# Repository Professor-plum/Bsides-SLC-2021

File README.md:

# Bsides-SLC-2021
Bsides SLC 2021 Badge repository

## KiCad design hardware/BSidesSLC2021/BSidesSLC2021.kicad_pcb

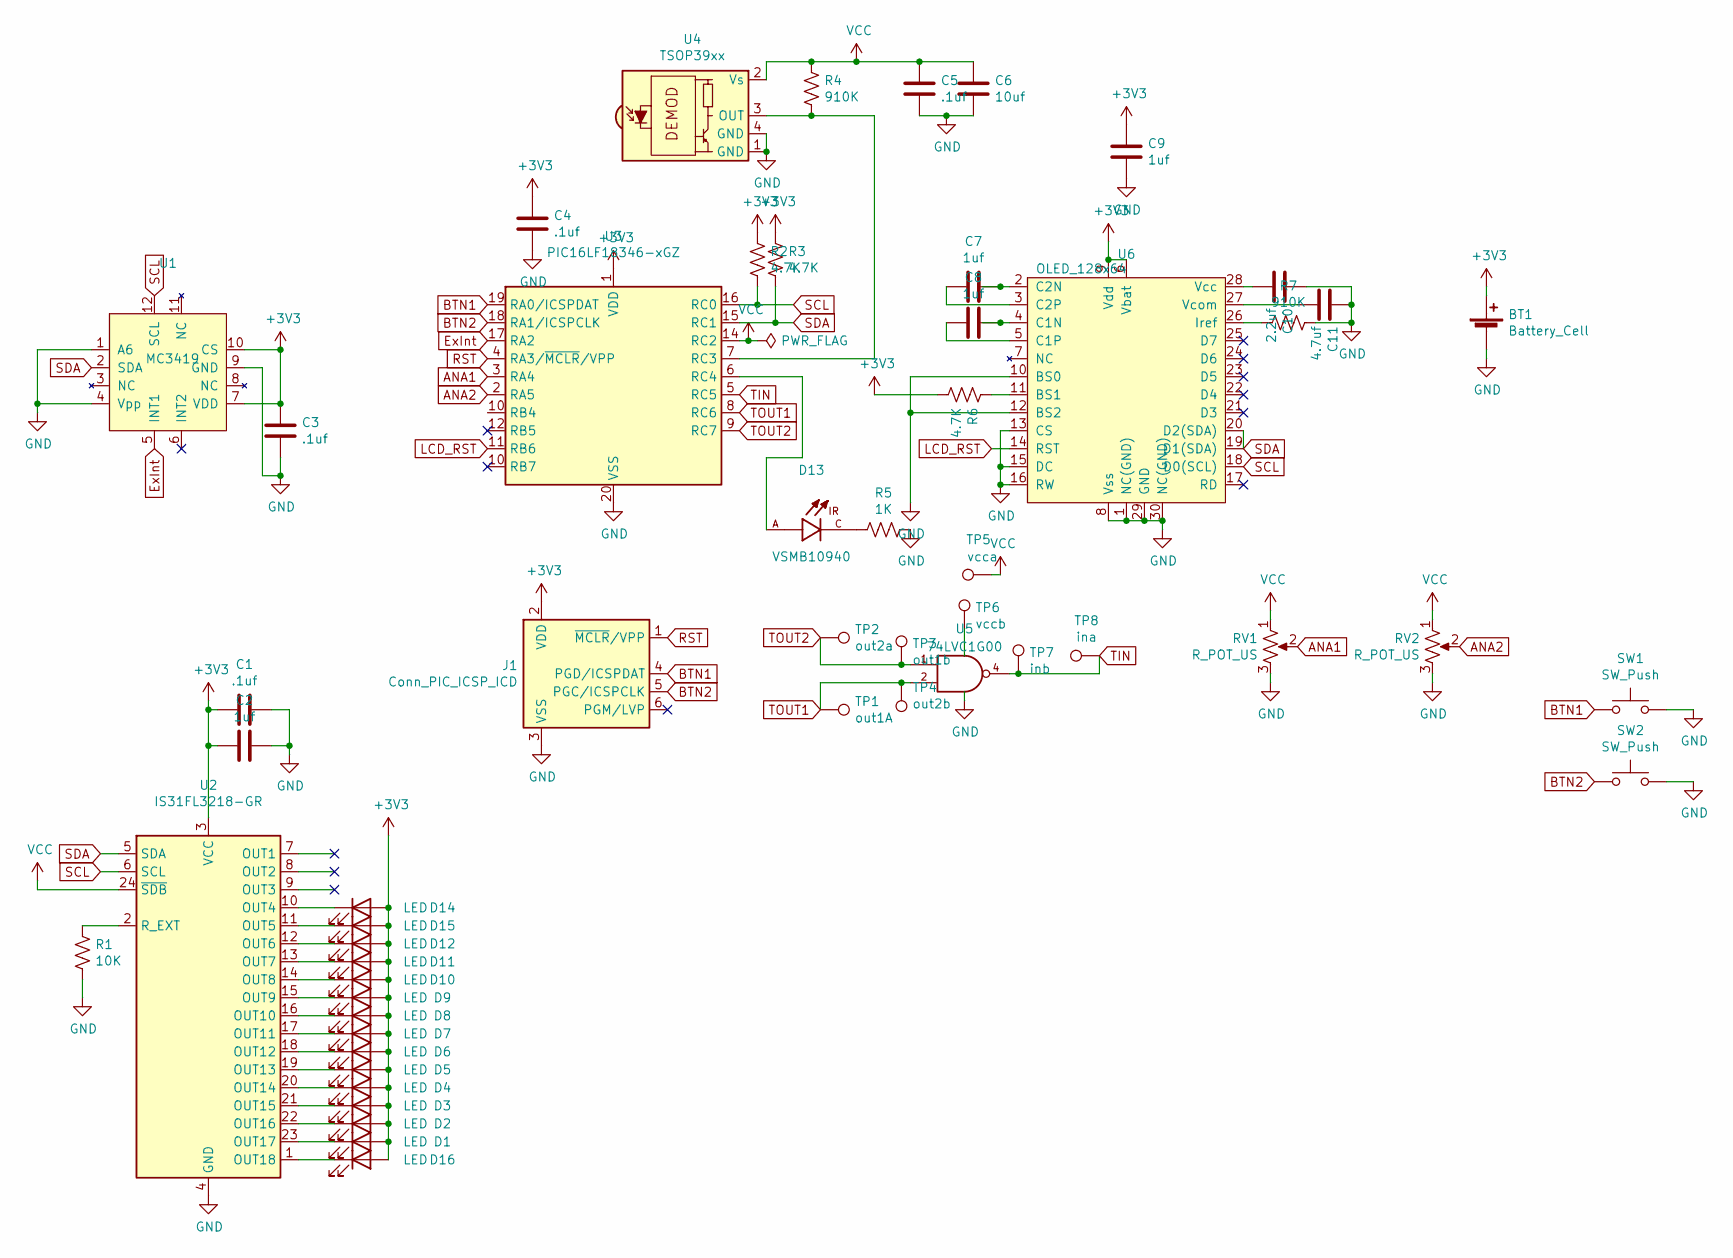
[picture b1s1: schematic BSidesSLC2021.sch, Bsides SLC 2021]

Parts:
BT1: Battery_Cell; BatteryHolder_Keystone_3034_1x20mm
C1, C3, C4, C5: .1uf; C_0603_1608Metric_Pad1.08x0.95mm_HandSolder
C2, C7, C8, C9: 1uf; C_0603_1608Metric_Pad1.08x0.95mm_HandSolder
C6: 10uf; C_0603_1608Metric_Pad1.08x0.95mm_HandSolder
C10: 2.2uf; C_0603_1608Metric_Pad1.08x0.95mm_HandSolder
C11: 4.7uf; C_0603_1608Metric_Pad1.08x0.95mm_HandSolder
D1, D2, D3, D4, D5, D6, D7, D8, D9, D10, D11, D12, D14, D15, D16: LED; LED_0603_1608Metric
D13: VSMB10940; DIO_VSMB10940; PARTREV 1.1
J1: Conn_PIC_ICSP_ICD; Batt_Conn5
R1: 10K; R_0603_1608Metric
R2, R3, R6: 4.7K; R_0603_1608Metric
R4, R7: 910K; R_0603_1608Metric
R5: 1K; R_0603_1608Metric
RV1, RV2: R_POT_US; Potentiometer_Bourns_PTV09A-1_Single_Vertical
SW1, SW2: SW_Push; SW_SPST_PTS645
TP1: out1A; TestPoint_Pad_D1.0mm
TP2: out2a; TestPoint_Pad_D1.0mm
TP3: out1b; TestPoint_Pad_D1.0mm
TP4: out2b; TestPoint_Pad_D1.0mm
TP5: vcca; TestPoint_Pad_D1.0mm
TP6: vccb; TestPoint_Pad_D1.0mm
TP7: inb; TestPoint_Pad_D1.0mm
TP8: ina; TestPoint_Pad_D1.0mm
U1: MC3419; LGA-12_2x2mm_P0.5mm
U2: IS31FL3218-GR; SOP-24_7.5x15.4mm_P1.27mm
U3: PIC16LF18346-xGZ; SSOP-20_5.3x7.2mm_P0.65mm
U4: TSOP39xx; TSOP392TR1
U5: 74LVC1G00; SOT-353_SC-70-5
U6: OLED_128x64; SSD1306_ribbon

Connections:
+3V3: BT1.1 (+), C1.1, C2.2, C3.2, C4.2, C9.2, D1.2 (A), D2.2 (A), D3.2 (A), D4.2 (A), D5.2 (A), D6.2 (A), D7.2 (A), D8.2 (A), D9.2 (A), D10.2 (A), D11.2 (A), D12.2 (A), D14.2 (A), D15.2 (A), D16.2 (A), J1.2 (VDD), R2.1, R3.1, R6.2, U1.7 (VDD), U1.10 (CS), U2.3 (VCC), U3.1 (VDD), U6.6 (Vbat), U6.9 (Vdd)
ANA1: RV1.2, U3.3 (RA4)
ANA2: RV2.2, U3.2 (RA5)
BTN1: J1.4 (PGD/ICSPDAT), SW1.1, U3.19 (RA0/ICSPDAT)
BTN2: J1.5 (PGC/ICSPCLK), SW2.1, U3.18 (RA1/ICSPCLK)
ExInt: U1.5 (INT1), U3.17 (RA2)
GND: BT1.2 (-), C1.2, C2.1, C3.1, C4.1, C5.1, C6.1, C9.1, C10.2, C11.2, J1.3 (VSS), R1.1, R5.1, R7.1, RV1.3, RV2.3, SW1.2, SW2.2, U1.1 (A6), U1.4 (Vpp), U1.9 (GND), U2.4 (GND), U3.20 (VSS), U4.1 (GND), U4.4 (GND), U5.3 (GND), U6.1 (NC(GND)), U6.8 (Vss), U6.10 (BS0), U6.12 (BS2), U6.13 (CS), U6.15 (DC), U6.16 (RW), U6.29 (GND), U6.30 (NC(GND))
LCD_RST: U3.11 (RB6), U6.14 (RST)
unnamed: C7.1, U6.2 (C2N)
unnamed: C7.2, U6.3 (C2P)
unnamed: C8.1, U6.4 (C1N)
unnamed: C8.2, U6.5 (C1P)
unnamed: C10.1, U6.28 (Vcc)
unnamed: C11.1, U6.27 (Vcom)
unnamed: D1.1 (K), U2.23 (OUT17)
unnamed: D2.1 (K), U2.22 (OUT16)
unnamed: D3.1 (K), U2.21 (OUT15)
unnamed: D4.1 (K), U2.20 (OUT14)
unnamed: D5.1 (K), U2.19 (OUT13)
unnamed: D6.1 (K), U2.18 (OUT12)
unnamed: D7.1 (K), U2.17 (OUT11)
unnamed: D8.1 (K), U2.16 (OUT10)
unnamed: D9.1 (K), U2.15 (OUT9)
unnamed: D10.1 (K), U2.14 (OUT8)
unnamed: D11.1 (K), U2.13 (OUT7)
unnamed: D12.1 (K), U2.12 (OUT6)
unnamed: D13.A, U3.6 (RC4)
unnamed: D13.C, R5.2
unnamed: D14.1 (K), U2.10 (OUT4)
unnamed: D15.1 (K), U2.11 (OUT5)
unnamed: D16.1 (K), U2.1 (OUT18)
unnamed: R1.2, U2.2 (R_EXT)
unnamed: R4.2, U3.7 (RC3), U4.3 (OUT)
unnamed: R6.1, U6.11 (BS1)
unnamed: R7.2, U6.26 (Iref)
RST: J1.1 (~MCLR~/VPP), U3.4 (RA3/~MCLR~/VPP)
SCL: R2.2, U1.12 (SCL), U2.6 (SCL), U3.16 (RC0), U6.18 (D0(SCL))
SDA: R3.2, U1.2 (SDA), U2.5 (SDA), U3.15 (RC1), U6.19 (D1(SDA)), U6.20 (D2(SDA))
TIN: TP7.1, TP8.1, U3.5 (RC5), U5.4
TOUT1: TP1.1, TP4.1, U3.8 (RC6), U5.2
TOUT2: TP2.1, TP3.1, U3.9 (RC7), U5.1

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
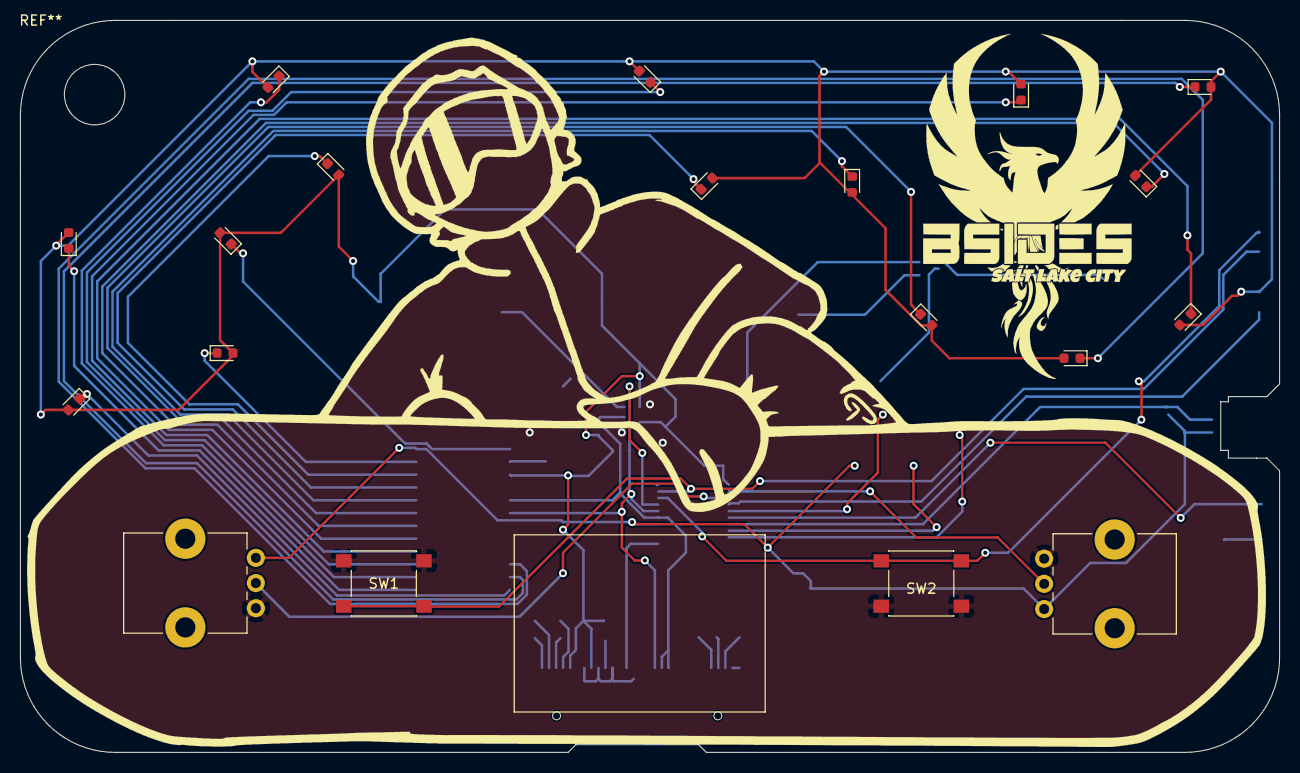
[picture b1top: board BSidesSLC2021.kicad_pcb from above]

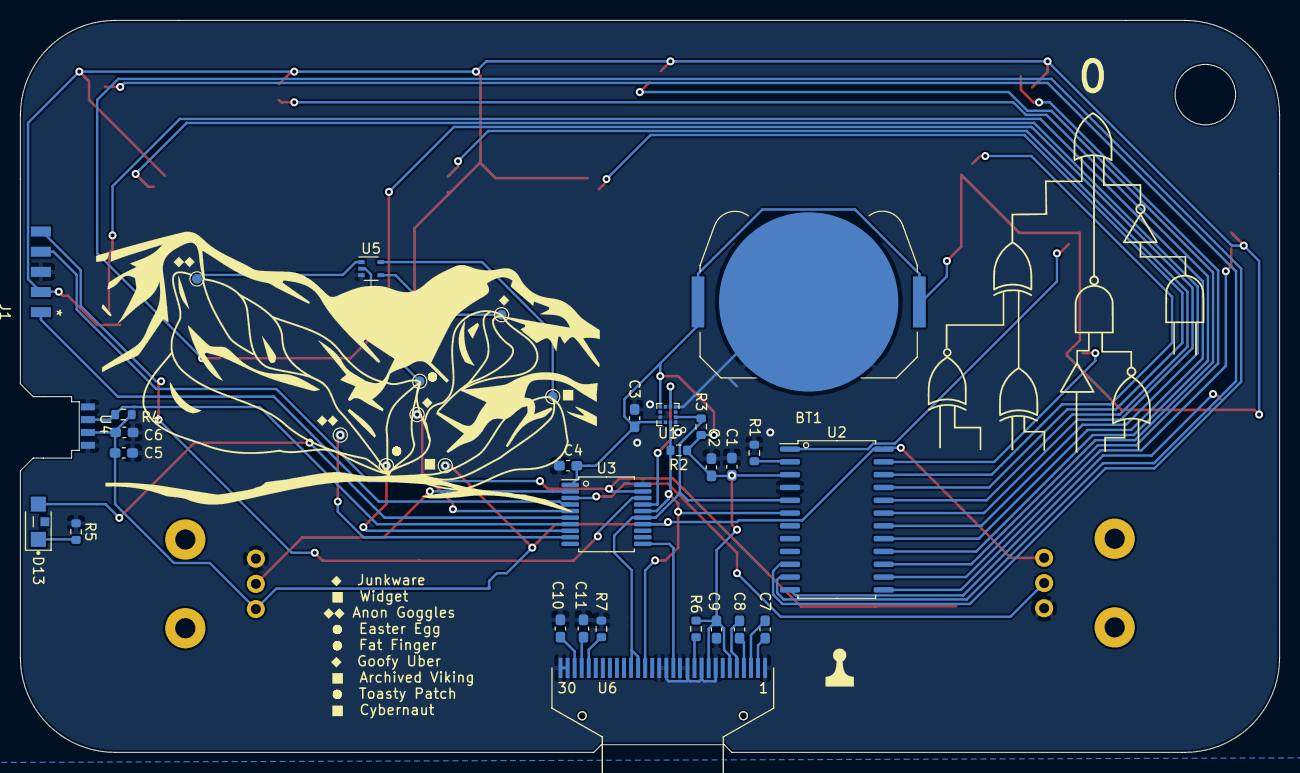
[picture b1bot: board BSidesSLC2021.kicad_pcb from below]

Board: 2 copper layers, 125.0 x 72.6 mm, 59 parts (38 on the bottom side), 42 nets.

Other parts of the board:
Ref**: Val**; logo_pheonix
Ref**#2: Val**; tree
Ref**#3: Val**; mtn2
Ref**#4: Val**; boarder
Ref**#5: Val**; plum

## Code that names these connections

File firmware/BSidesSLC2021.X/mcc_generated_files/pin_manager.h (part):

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// get/set IO_RA0 aliases
#define IO_RA0_TRIS                 TRISAbits.TRISA0
#define IO_RA0_LAT                  LATAbits.LATA0
#define IO_RA0_PORT                 PORTAbits.RA0
#define IO_RA0_WPU                  WPUAbits.WPUA0
#define IO_RA0_OD                   ODCONAbits.ODCA0
#define IO_RA0_ANS                  ANSELAbits.ANSA0
#define IO_RA0_SetHigh()            do { LATAbits.LATA0 = 1; } while(0)
#define IO_RA0_SetLow()             do { LATAbits.LATA0 = 0; } while(0)
#define IO_RA0_Toggle()             do { LATAbits.LATA0 = ~LATAbits.LATA0; } while(0)
#define IO_RA0_GetValue()           PORTAbits.RA0
#define IO_RA0_SetDigitalInput()    do { TRISAbits.TRISA0 = 1; } while(0)
#define IO_RA0_SetDigitalOutput()   do { TRISAbits.TRISA0 = 0; } while(0)
#define IO_RA0_SetPullup()          do { WPUAbits.WPUA0 = 1; } while(0)
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// get/set IO_RA1 aliases
#define IO_RA1_TRIS                 TRISAbits.TRISA1
#define IO_RA1_LAT                  LATAbits.LATA1
#define IO_RA1_PORT                 PORTAbits.RA1
#define IO_RA1_WPU                  WPUAbits.WPUA1
#define IO_RA1_OD                   ODCONAbits.ODCA1
#define IO_RA1_ANS                  ANSELAbits.ANSA1
#define IO_RA1_SetHigh()            do { LATAbits.LATA1 = 1; } while(0)
#define IO_RA1_SetLow()             do { LATAbits.LATA1 = 0; } while(0)
#define IO_RA1_Toggle()             do { LATAbits.LATA1 = ~LATAbits.LATA1; } while(0)
#define IO_RA1_GetValue()           PORTAbits.RA1
#define IO_RA1_SetDigitalInput()    do { TRISAbits.TRISA1 = 1; } while(0)
#define IO_RA1_SetDigitalOutput()   do { TRISAbits.TRISA1 = 0; } while(0)
#define IO_RA1_SetPullup()          do { WPUAbits.WPUA1 = 1; } while(0)
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#define RA2_SetHigh()            do { LATAbits.LATA2 = 1; } while(0)
#define RA2_SetLow()             do { LATAbits.LATA2 = 0; } while(0)
#define RA2_Toggle()             do { LATAbits.LATA2 = ~LATAbits.LATA2; } while(0)
#define RA2_GetValue()              PORTAbits.RA2
#define RA2_SetDigitalInput()    do { TRISAbits.TRISA2 = 1; } while(0)
#define RA2_SetDigitalOutput()   do { TRISAbits.TRISA2 = 0; } while(0)
#define RA2_SetPullup()             do { WPUAbits.WPUA2 = 1; } while(0)
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// get/set channel_ANA4 aliases
#define channel_ANA4_TRIS                 TRISAbits.TRISA4
#define channel_ANA4_LAT                  LATAbits.LATA4
#define channel_ANA4_PORT                 PORTAbits.RA4
#define channel_ANA4_WPU                  WPUAbits.WPUA4
#define channel_ANA4_OD                   ODCONAbits.ODCA4
#define channel_ANA4_ANS                  ANSELAbits.ANSA4
#define channel_ANA4_SetHigh()            do { LATAbits.LATA4 = 1; } while(0)
#define channel_ANA4_SetLow()             do { LATAbits.LATA4 = 0; } while(0)
#define channel_ANA4_Toggle()             do { LATAbits.LATA4 = ~LATAbits.LATA4; } while(0)
#define channel_ANA4_GetValue()           PORTAbits.RA4
#define channel_ANA4_SetDigitalInput()    do { TRISAbits.TRISA4 = 1; } while(0)
#define channel_ANA4_SetDigitalOutput()   do { TRISAbits.TRISA4 = 0; } while(0)
#define channel_ANA4_SetPullup()          do { WPUAbits.WPUA4 = 1; } while(0)
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// get/set channel_ANA5 aliases
#define channel_ANA5_TRIS                 TRISAbits.TRISA5
#define channel_ANA5_LAT                  LATAbits.LATA5
#define channel_ANA5_PORT                 PORTAbits.RA5
#define channel_ANA5_WPU                  WPUAbits.WPUA5
#define channel_ANA5_OD                   ODCONAbits.ODCA5
#define channel_ANA5_ANS                  ANSELAbits.ANSA5
#define channel_ANA5_SetHigh()            do { LATAbits.LATA5 = 1; } while(0)
#define channel_ANA5_SetLow()             do { LATAbits.LATA5 = 0; } while(0)
#define channel_ANA5_Toggle()             do { LATAbits.LATA5 = ~LATAbits.LATA5; } while(0)
#define channel_ANA5_GetValue()           PORTAbits.RA5
#define channel_ANA5_SetDigitalInput()    do { TRISAbits.TRISA5 = 1; } while(0)
#define channel_ANA5_SetDigitalOutput()   do { TRISAbits.TRISA5 = 0; } while(0)
#define channel_ANA5_SetPullup()          do { WPUAbits.WPUA5 = 1; } while(0)
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// get/set IO_RB6 aliases
#define IO_RB6_TRIS                 TRISBbits.TRISB6
#define IO_RB6_LAT                  LATBbits.LATB6
#define IO_RB6_PORT                 PORTBbits.RB6
#define IO_RB6_WPU                  WPUBbits.WPUB6
#define IO_RB6_OD                   ODCONBbits.ODCB6
#define IO_RB6_ANS                  ANSELBbits.ANSB6
#define IO_RB6_SetHigh()            do { LATBbits.LATB6 = 1; } while(0)
#define IO_RB6_SetLow()             do { LATBbits.LATB6 = 0; } while(0)
#define IO_RB6_Toggle()             do { LATBbits.LATB6 = ~LATBbits.LATB6; } while(0)
#define IO_RB6_GetValue()           PORTBbits.RB6
#define IO_RB6_SetDigitalInput()    do { TRISBbits.TRISB6 = 1; } while(0)
#define IO_RB6_SetDigitalOutput()   do { TRISBbits.TRISB6 = 0; } while(0)
#define IO_RB6_SetPullup()          do { WPUBbits.WPUB6 = 1; } while(0)
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#define RC0_SetHigh()            do { LATCbits.LATC0 = 1; } while(0)
#define RC0_SetLow()             do { LATCbits.LATC0 = 0; } while(0)
#define RC0_Toggle()             do { LATCbits.LATC0 = ~LATCbits.LATC0; } while(0)
#define RC0_GetValue()              PORTCbits.RC0
#define RC0_SetDigitalInput()    do { TRISCbits.TRISC0 = 1; } while(0)
#define RC0_SetDigitalOutput()   do { TRISCbits.TRISC0 = 0; } while(0)
#define RC0_SetPullup()             do { WPUCbits.WPUC0 = 1; } while(0)
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#define RC1_SetHigh()            do { LATCbits.LATC1 = 1; } while(0)
#define RC1_SetLow()             do { LATCbits.LATC1 = 0; } while(0)
#define RC1_Toggle()             do { LATCbits.LATC1 = ~LATCbits.LATC1; } while(0)
#define RC1_GetValue()              PORTCbits.RC1
#define RC1_SetDigitalInput()    do { TRISCbits.TRISC1 = 1; } while(0)
#define RC1_SetDigitalOutput()   do { TRISCbits.TRISC1 = 0; } while(0)
#define RC1_SetPullup()             do { WPUCbits.WPUC1 = 1; } while(0)
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// get/set IO_RC2 aliases
#define IO_RC2_TRIS                 TRISCbits.TRISC2
#define IO_RC2_LAT                  LATCbits.LATC2
#define IO_RC2_PORT                 PORTCbits.RC2
#define IO_RC2_WPU                  WPUCbits.WPUC2
#define IO_RC2_OD                   ODCONCbits.ODCC2
#define IO_RC2_ANS                  ANSELCbits.ANSC2
#define IO_RC2_SetHigh()            do { LATCbits.LATC2 = 1; } while(0)
#define IO_RC2_SetLow()             do { LATCbits.LATC2 = 0; } while(0)
#define IO_RC2_Toggle()             do { LATCbits.LATC2 = ~LATCbits.LATC2; } while(0)
#define IO_RC2_GetValue()           PORTCbits.RC2
#define IO_RC2_SetDigitalInput()    do { TRISCbits.TRISC2 = 1; } while(0)
#define IO_RC2_SetDigitalOutput()   do { TRISCbits.TRISC2 = 0; } while(0)
#define IO_RC2_SetPullup()          do { WPUCbits.WPUC2 = 1; } while(0)
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// get/set IO_RC3 aliases
#define IO_RC3_TRIS                 TRISCbits.TRISC3
#define IO_RC3_LAT                  LATCbits.LATC3
#define IO_RC3_PORT                 PORTCbits.RC3
#define IO_RC3_WPU                  WPUCbits.WPUC3
#define IO_RC3_OD                   ODCONCbits.ODCC3
#define IO_RC3_ANS                  ANSELCbits.ANSC3
#define IO_RC3_SetHigh()            do { LATCbits.LATC3 = 1; } while(0)
#define IO_RC3_SetLow()             do { LATCbits.LATC3 = 0; } while(0)
#define IO_RC3_Toggle()             do { LATCbits.LATC3 = ~LATCbits.LATC3; } while(0)
#define IO_RC3_GetValue()           PORTCbits.RC3
#define IO_RC3_SetDigitalInput()    do { TRISCbits.TRISC3 = 1; } while(0)
#define IO_RC3_SetDigitalOutput()   do { TRISCbits.TRISC3 = 0; } while(0)
#define IO_RC3_SetPullup()          do { WPUCbits.WPUC3 = 1; } while(0)
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#define RC4_SetHigh()            do { LATCbits.LATC4 = 1; } while(0)
#define RC4_SetLow()             do { LATCbits.LATC4 = 0; } while(0)
#define RC4_Toggle()             do { LATCbits.LATC4 = ~LATCbits.LATC4; } while(0)
#define RC4_GetValue()              PORTCbits.RC4
#define RC4_SetDigitalInput()    do { TRISCbits.TRISC4 = 1; } while(0)
#define RC4_SetDigitalOutput()   do { TRISCbits.TRISC4 = 0; } while(0)
#define RC4_SetPullup()             do { WPUCbits.WPUC4 = 1; } while(0)
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// get/set IO_RC5 aliases
#define IO_RC5_TRIS                 TRISCbits.TRISC5
#define IO_RC5_LAT                  LATCbits.LATC5
#define IO_RC5_PORT                 PORTCbits.RC5
#define IO_RC5_WPU                  WPUCbits.WPUC5
#define IO_RC5_OD                   ODCONCbits.ODCC5
#define IO_RC5_ANS                  ANSELCbits.ANSC5
#define IO_RC5_SetHigh()            do { LATCbits.LATC5 = 1; } while(0)
#define IO_RC5_SetLow()             do { LATCbits.LATC5 = 0; } while(0)
#define IO_RC5_Toggle()             do { LATCbits.LATC5 = ~LATCbits.LATC5; } while(0)
#define IO_RC5_GetValue()           PORTCbits.RC5
#define IO_RC5_SetDigitalInput()    do { TRISCbits.TRISC5 = 1; } while(0)
#define IO_RC5_SetDigitalOutput()   do { TRISCbits.TRISC5 = 0; } while(0)
#define IO_RC5_SetPullup()          do { WPUCbits.WPUC5 = 1; } while(0)
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// get/set IO_RC6 aliases
#define IO_RC6_TRIS                 TRISCbits.TRISC6
#define IO_RC6_LAT                  LATCbits.LATC6
#define IO_RC6_PORT                 PORTCbits.RC6
#define IO_RC6_WPU                  WPUCbits.WPUC6
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
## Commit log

2021-11-02 Added firmware to repository
2021-11-02 Kicad files added to repo
2021-11-02 Removed local settings files from firmware repo
2021-11-08 Space optimizations, and finishing touches
2021-11-09 Firmware ready for release

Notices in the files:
firmware/BSidesSLC2021.X/mcc_generated_files/pin_manager.h:
(c) 2018 Microchip Technology Inc. and its subsidiaries.
